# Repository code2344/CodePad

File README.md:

CodePad is a small 3-key macropad for coding. It integrates with Visual Studio Code to show things such as git commit status, unsaved files, bugs, and more. The keys change depending on the program, but for now they are Save, Save All, and git commit (will AI-generate a commit message).
BOM:
|Reference|Qty|Value|DNP|Exclude from BOM|Exclude from Board|Footprint|Datasheet|
|---|---|---|---|---|---|---|---|
|D1,D2,D3,D4,D5,D6,D7,D8|8|SK6812MINI-E||||footprints:SK6812MINI-E_fixed|https://cdn-shop.adafruit.com/product-files/4960/4960_SK6812MINI-E_REV02_EN.pdf|
|R1|1|330R||||Resistor_SMD:R_0603_1608Metric|~|
|SW1,SW2,SW3|3|SW_Push||||Button_Switch_Keyboard:SW_Cherry_MX_1.00u_PCB|~|
|U1|1|MOUDLE-SEEEDUINO-XIAO||||footprints:XIAO-Generic-Hybrid-14P-2.54-21X17.8MM||

Firmware is written in circuitpython.

---
AI declaration: I have used AI for commit messages to this repo, and to fix the organisational structure. this is the only AI use in this project.

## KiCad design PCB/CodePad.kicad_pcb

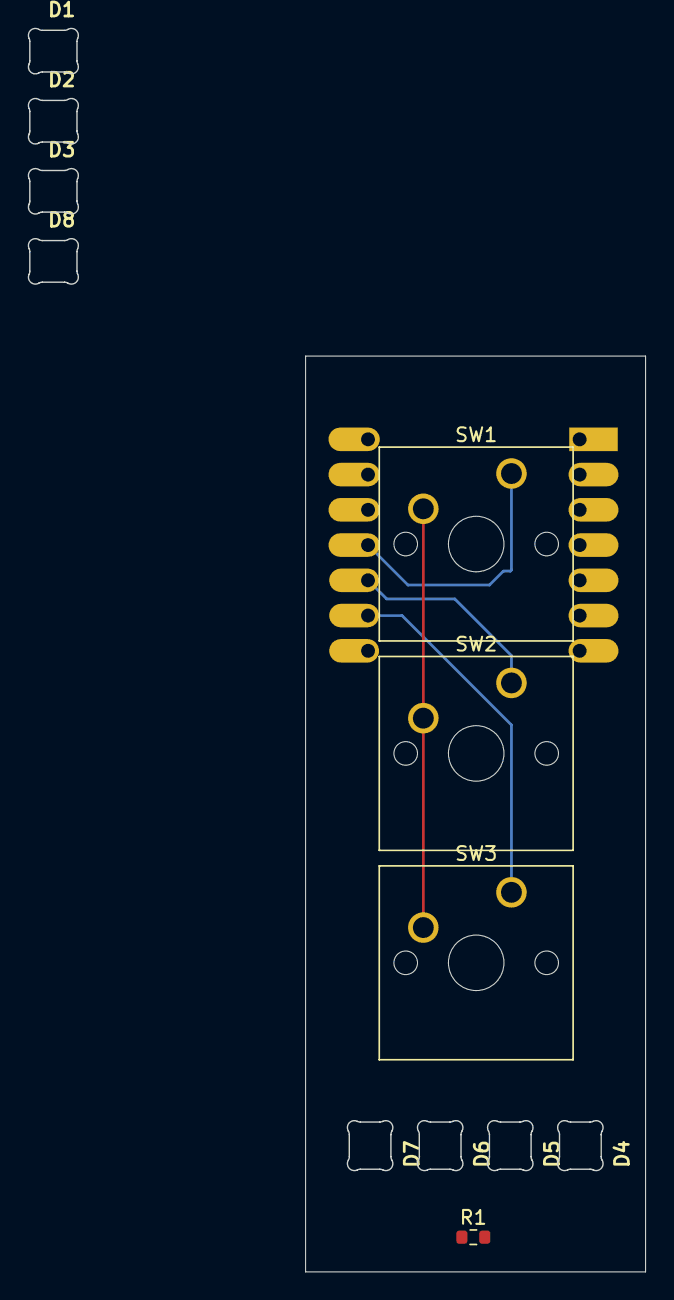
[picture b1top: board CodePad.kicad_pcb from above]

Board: 2 copper layers, 44.5 x 89.6 mm, 13 parts (1 on the bottom side), 10 nets.

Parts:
D1, D2, D3, D4, D5, D6, D7, D8: SK6812MINI-E; SK6812MINI-E_fixed
R1: 330R; R_0603_1608Metric
SW1, SW2, SW3: SW_Push; SW_Cherry_MX_1.00u_PCB
U1: MOUDLE-SEEEDUINO-XIAO; XIAO-Generic-Hybrid-14P-2.54-21X17.8MM

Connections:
GND: D1.3 (VSS), D2.3 (VSS), D3.3 (VSS), D4.3 (VSS), D5.3 (VSS), D6.3 (VSS), D7.3 (VSS), D8.3 (VSS), SW1.2, SW2.2, SW3.2, U1.13 (GND)
unnamed: D2.1 (VDD), D3.1 (VDD), D4.1 (VDD), D5.1 (VDD), D6.1 (VDD), D7.1 (VDD), D8.1 (VDD), U1.14 (5V)
unnamed: D4.4 (DIN), R1.2
unnamed: D4.2 (DOUT), D5.4 (DIN)
unnamed: D5.2 (DOUT), D6.4 (DIN)
unnamed: D6.2 (DOUT), D7.4 (DIN)
unnamed: R1.1, U1.2 (PA4_A1_D1)
unnamed: SW2.1, U1.10 (PA5_A9_D9_MISO)
unnamed: SW1.1, U1.11 (PA6_A10_D10_MOSI)
unnamed: SW3.1, U1.9 (PA7_A8_D8_SCK)

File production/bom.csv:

Designator,Footprint,Quantity,Value,LCSC Part #
"D1, D2, D3, D4, D5, D6, D7, D8",SK6812MINI-E_fixed,8,SK6812MINI-E,
R1,0603,1,330R,
"SW1, SW2, SW3",SW_Cherry_MX_1.00u_PCB,3,SW_Push,

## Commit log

2026-03-05 add main
2026-03-05 add README.md with project description and BOM details
2026-03-05 format BOM table in README.md for better readability
2026-03-05 fix formatting of BOM table in README.md for consistency
2026-03-05 Add lock file for KiCad project with hostname and username
2026-03-05 Add AI declaration to README.md for transparency on commit message generation
2026-03-05 fix formatting in README.md to improve structure and readability
2026-03-05 Refactor code structure for improved readability and maintainability
2026-03-05 Add BOM and CodePad CSV files for component management
2026-03-06 Remove unnecessary .DS_Store file from production directory and reogr
